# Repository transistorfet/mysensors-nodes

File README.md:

MySensors Nodes
===============

###### *Started ~March 31, 2015*

Some Arduino sketches that use the [MySensors](https://www.mysensors.org/) library to set up a
network of nodes that can be controlled through [Nerve](https://jabberwocky.ca/projects/nerve/).
Most of these were set up around 2015/2016, but I've recently made a simple PCB to replace the
breadboarded versions scattered around my house.

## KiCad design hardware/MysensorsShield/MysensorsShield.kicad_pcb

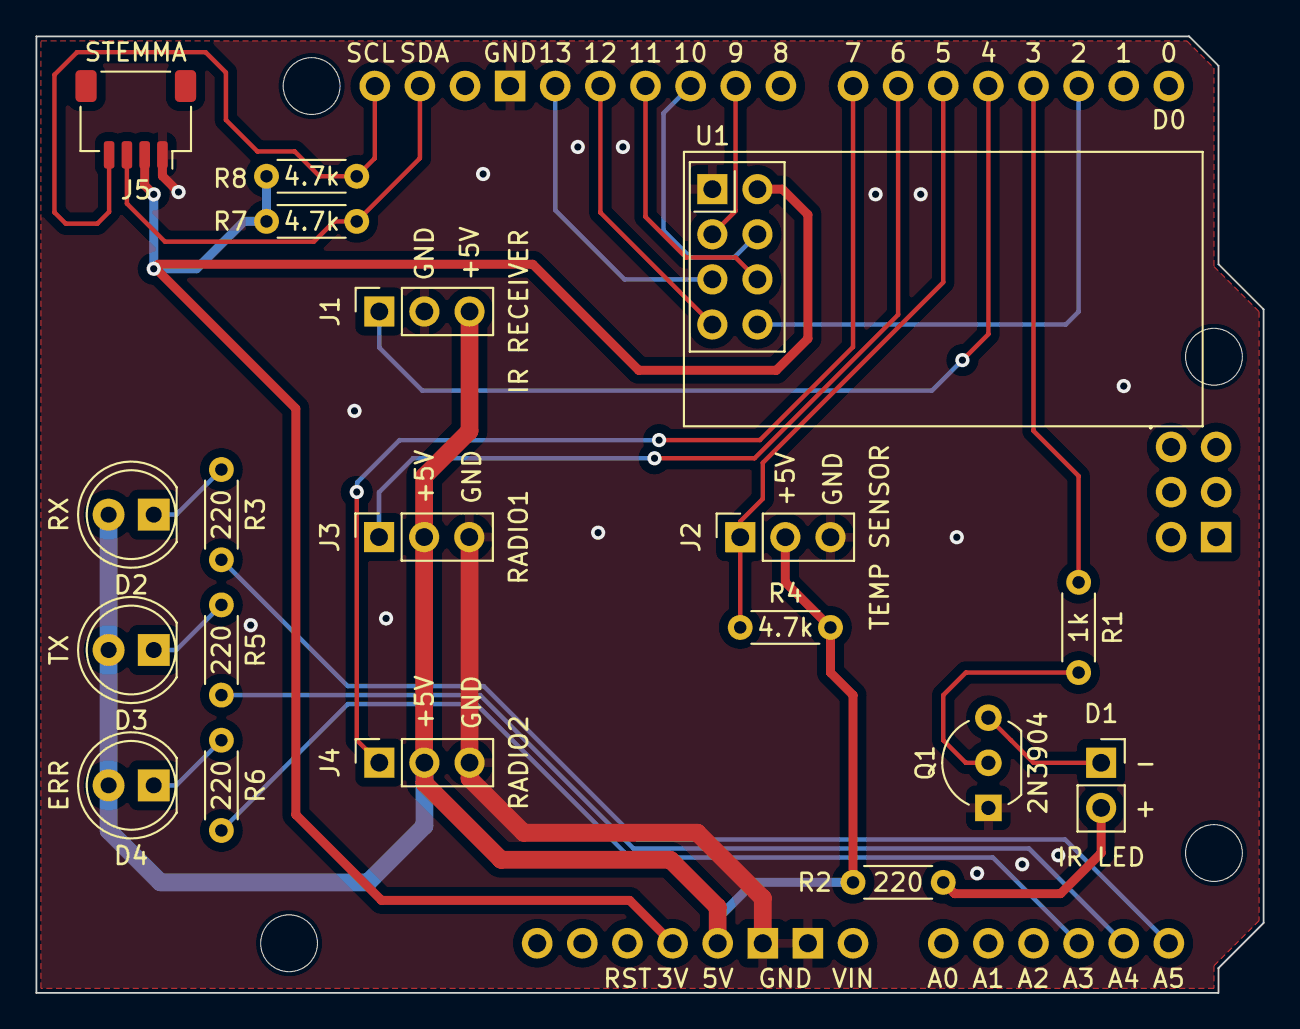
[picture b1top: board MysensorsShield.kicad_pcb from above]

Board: 2 copper layers, 69.1 x 53.8 mm, 20 parts (0 on the bottom side), 25 nets.

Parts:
A1: Arduino_Uno_R3_Shield
D1: IR LED; PinSocket_1x02_P2.54mm_Vertical
D2: RX; LED_D5.0mm
D3: TX; LED_D5.0mm
D4: ERR; LED_D5.0mm
J1: IR RECEIVER; PinSocket_1x03_P2.54mm_Vertical
J2: TEMP SENSOR; PinSocket_1x03_P2.54mm_Vertical
J3: RADIO1; PinSocket_1x03_P2.54mm_Vertical
J4: RADIO2; PinSocket_1x03_P2.54mm_Vertical
J5: STEMMA; JST_SH_SM04B-SRSS-TB_1x04-1MP_P1.00mm_Horizontal
Q1: 2N3904; TO-92_Inline_Wide
R1: 1k; R_Axial_DIN0204_L3.6mm_D1.6mm_P5.08mm_Horizontal
R2, R3, R5, R6: 220; R_Axial_DIN0204_L3.6mm_D1.6mm_P5.08mm_Horizontal
R4, R7, R8: 4.7k; R_Axial_DIN0204_L3.6mm_D1.6mm_P5.08mm_Horizontal
U1: NRF24L01_Breakout; nRF24L01_Breakout

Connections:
+3.3V: A1.3V3 (3.3V), J5.2, R7.1, R8.1, U1.2 (VCC)
+5V: A1.5V1 (5V), D2.2 (A), D3.2 (A), D4.2 (A), J1.3, J2.2, J3.2, J4.2, R2.1, R4.2
CE: A1.D9, U1.3 (CE)
GND: A1.GND1 (GND), A1.GND2 (GND), A1.GND3 (GND), J1.2, J2.3, J3.3, J4.3, J5.1, Q1.1 (E), U1.1 (GND)
IRQ: A1.D2 (D2_INT0), U1.8 (IRQ)
IR_IN: A1.D4, J1.1
IR_OUT: A1.D3 (D3_INT1), R1.1
unnamed: A1.A3, R6.2
unnamed: A1.A4, R5.2
unnamed: A1.A5, R3.2
unnamed: D1.2 (A), R2.2
unnamed: D1.1 (K), Q1.3 (C)
unnamed: D2.1 (K), R3.1
unnamed: D3.1 (K), R5.1
unnamed: D4.1 (K), R6.1
unnamed: Q1.2 (B), R1.2
R1_IO: A1.D6, J3.1
R2_IO: A1.D7, J4.1
SCK: A1.D13, U1.5 (SCK)
SCL: A1.SCL, J5.4, R8.2
SDA: A1.SDA, J5.3, R7.2
SDI: A1.D11, U1.6 (MOSI)
SDO: A1.D12, U1.7 (MISO)
T_1WR: A1.D5, J2.1, R4.1
~CS: A1.D10 (D10_CS), U1.4 (~CSN)

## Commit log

2023-12-17 Added existing project files, originally started in 2015
2023-12-28 Added multipurpose arduino shield to replace the existing breadboard nodes
2023-12-28 Added readme
2023-12-30 MultiPurposeNode Rev.1 shield complete
2024-01-07 Reorganized and fixed node programs to use the new multipurpose shield
2024-04-22 Added serial gateway with IR send/recv using MySensors2
